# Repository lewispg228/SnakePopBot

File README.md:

OpenSnake
========================================

OpenSnake is the opensource firmware and design files that are used to produce the Electronic Snake In A Can Kit. It is a collaboration between Mario the Maker Magician and Jumping Snakes Engineering.

The classic snake-in-a-can gag meets DIY MAGIC! With this kit, you'll assemble an Electronic Snake-in-a-Can, introducing you to the world of programming, robotics, and how these tools can be used to create surprise, magic, and comedy.

* includes CONTROLLER for PLAYBACK and RECORDER of robotic magic tricks\
* RE-PROGRAMMABLE with ARDUINO
* learn about SERVOS, BUZZERS, BUTTONS, and LEDs
* pre-programmed with a magic routine written by Mario, PLUS you can make your own
* note: requires 9V battery (not included)

Buy this kit at Mario The Maker Magician's website here:

[BUY KIT HERE](https://www.mariothemagician.com/product-page/electronic-snake-in-a-can-kit)

The magic trick "skit" that is included as track one in the firmware can be watched here on Mario's Instagram post:

[INSTAGRAM VIDEO](https://www.instagram.com/tv/CCRtKZynAKZ/)

Repository Contents
-------------------

* **/Documentation** - assembly instructions, pictures, additional product information
* **/Firmware** - Arduino Code used on the snake-in-a-can controller
* **/Hardware** - Eagle design files (.brd, .sch)
* **/Hardware/Production** - Production panel files (.brd and gerbers)

License Information
-------------------

This product is _**open source**_! 

Please review the LICENSE.md file for license information. 

If you have any questions or concerns on licensing, please [file an issue on this repository](https://github.com/lewispg228/OpenSnake/issues), and we will respond asap.

Distributed as-is; no warranty is given.

- Jumping Snakes Engineering.

_<COLLABORATION CREDIT>_

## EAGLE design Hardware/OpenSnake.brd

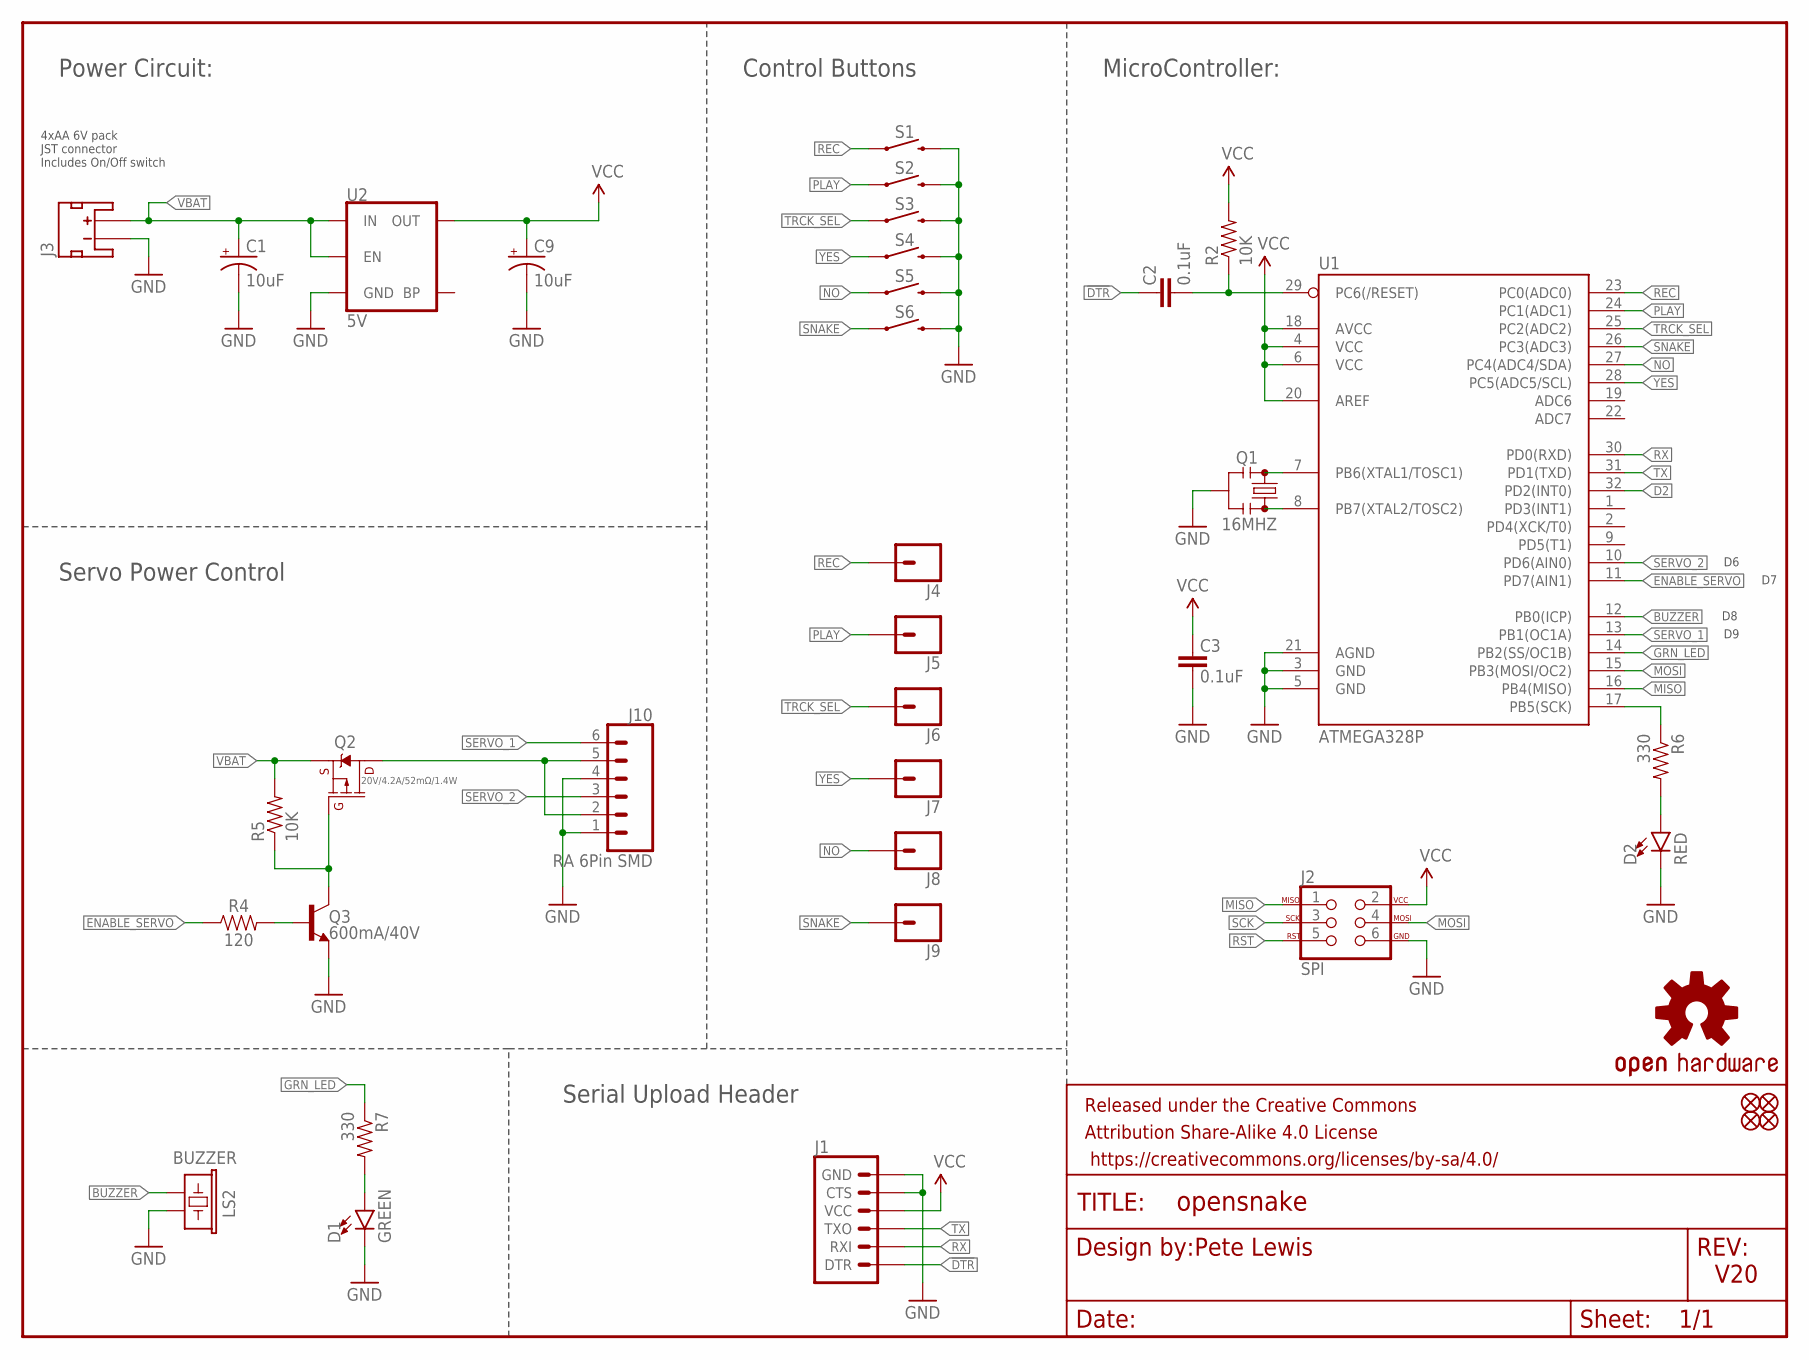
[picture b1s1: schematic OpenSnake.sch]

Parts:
C1, C9: 10uF; EIA3216
C2, C3: 0.1uF; 0603-CAP
D1: GREEN; LED-1206
D2: RED; LED-1206
FD1, FD2, FD3, FD4: FIDUCIALUFIDUCIAL; FIDUCIAL-MICRO
FRAME1: FRAME-LETTER; CREATIVE_COMMONS
J1: 6_PIN_SERIAL_TARGETSILK; 6_PIN_SERIAL_TARGET_SIDE_W_SILK
J2: SPI; 2X3_TEST_POINTS
J3: JST_2MM_MALE; JST-2-SMD
J4, J5, J6, J7, J8, J9: CONN_01PTH_NO_SILK_YES_STOP; 1X01_NO_SILK
J10: RA 6Pin SMD; 1X06-SMD_RA_MALE
LOGO1: OSHW-LOGOL; OSHW-LOGO-L
LS2: BUZZER; BUZZER-CCV
Q1: 16MHZ; RESONATOR-SMD
Q2: 20V/4.2A/52mΩ/1.4W; SOT23-3
Q3: 600mA/40V; SOT23-3
R2, R5: 10K; 0603-RES
R4: 120; 0603
R6, R7: 330; 0603-RES
S1, S2, S3, S4, S5, S6: MOMENTARY-SWITCH-SPST-SMD-5.2MM-TALL; TACTILE_SWITCH_SMD_5.2MM
U1: ATMEGA328P; TQFP32-08
U2: 5V; SOT23-5

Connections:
!DTR: C2.2, J1.P$1 (DTR)
BUZZER: LS2.- (2), U1.12 (PB0(ICP))
D2: U1.32 (PD2(INT0))
ENABLE_SERVO: R4.1, U1.11 (PD7(AIN1))
GND: C1.-, C3.1, C9.-, D1.C, D2.C, J1.P$5 (CTS), J1.P$6 (GND), J2.6, J3.1 (-), J10.1, J10.4, LS2.+ (1), Q1.2, Q3.2 (E), S1.3 (2), S2.3 (2), S3.3 (2), S4.3 (2), S5.3 (2), S6.3 (2), U1.3 (GND), U1.5 (GND), U1.21 (AGND), U2.2 (GND)
GRN_LED: R7.1, U1.14 (PB2(SS/OC1B))
MISO: J2.1, U1.16 (PB4(MISO))
MOSI: J2.4, U1.15 (PB3(MOSI/OC2))
unnamed: Q1.1, U1.8 (PB7(XTAL2/TOSC2))
unnamed: Q1.3, U1.7 (PB6(XTAL1/TOSC1))
unnamed: Q3.1 (B), R4.2
unnamed: Q2.1 (G), Q3.3 (C), R5.1
unnamed: J10.2, J10.5, Q2.3 (D)
unnamed: D2.A, R6.2
unnamed: D1.A, R7.2
NO: J8.1, S5.1, U1.27 (PC4(ADC4/SDA))
PLAY: J5.1, S2.1, U1.24 (PC1(ADC1))
REC: J4.1, S1.1, U1.23 (PC0(ADC0))
RST: C2.1, J2.5, R2.1, U1.29 (PC6(/RESET))
RX: J1.P$3 (RXI), U1.30 (PD0(RXD))
SCK: J2.3, R6.1, U1.17 (PB5(SCK))
SERVO_1: J10.6, U1.13 (PB1(OC1A))
SERVO_2: J10.3, U1.10 (PD6(AIN0))
SNAKE: J9.1, S6.1, U1.26 (PC3(ADC3))
TRCK_SEL: J6.1, S3.1, U1.25 (PC2(ADC2))
TX: J1.P$2 (TXO), U1.31 (PD1(TXD))
VBAT: C1.+, J3.2 (+), Q2.2 (S), R5.2, U2.1 (IN), U2.3 (EN)
VCC: C3.2, C9.+, J1.P$4 (VCC), J2.2, R2.2, U1.4 (VCC), U1.6 (VCC), U1.18 (AVCC), U1.20 (AREF), U2.5 (OUT)
YES: J7.1, S4.1, U1.28 (PC5(ADC5/SCL))

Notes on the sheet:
V20
Pete Lewis
Power Circuit:
4xAA 6V pack JST connector Includes On/Off switch
MicroController:
Servo Power Control
Control Buttons
Serial Upload Header

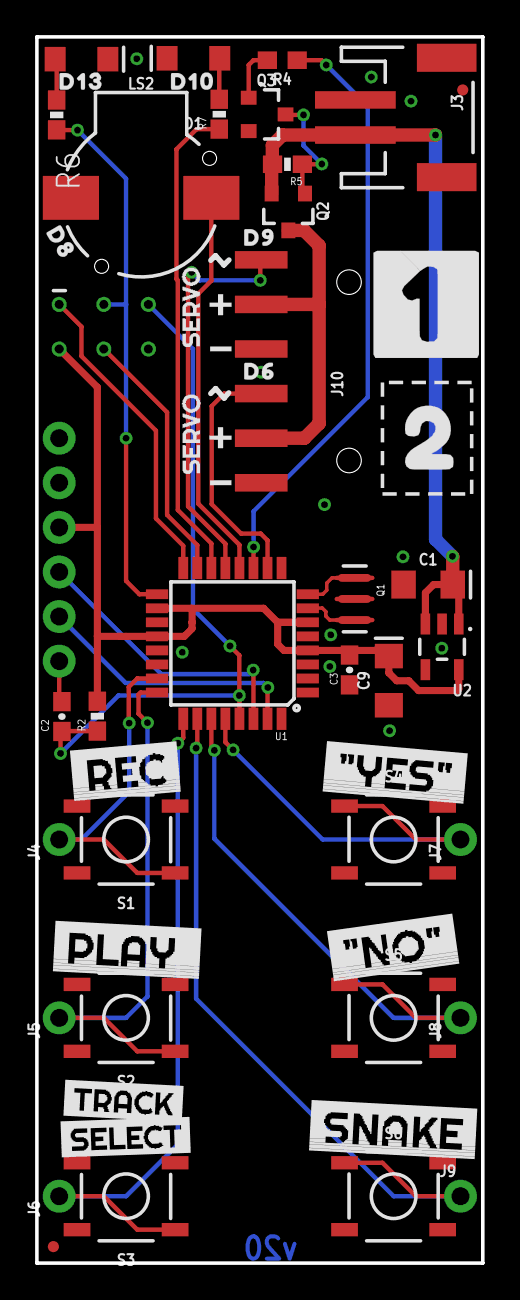
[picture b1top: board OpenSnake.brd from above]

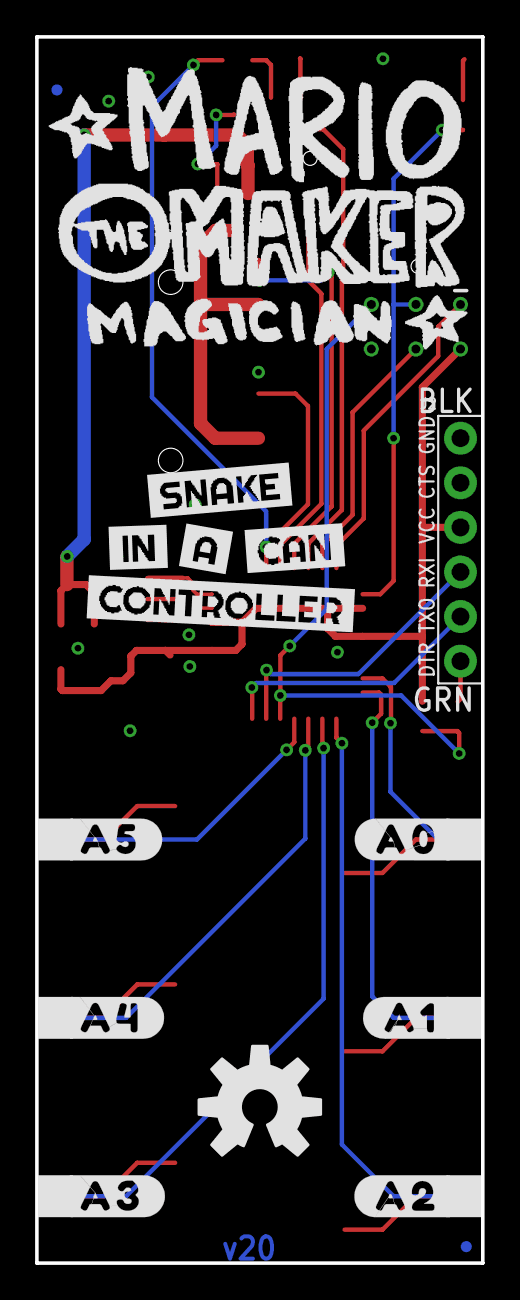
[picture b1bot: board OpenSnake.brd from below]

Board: 2 copper layers, 25.4 x 69.8 mm, 69 parts (17 on the bottom side), 28 nets.

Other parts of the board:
U$1: #A0#0
U$2: #YES#0
U$3: #NO#1
U$4: SNAKE2
U$5: MARIO_LOGO
U$6: #A1#0
U$7: #A2#0
U$8, U$13: SERVO2
U$9: #A3#0
U$10: #A4#0
U$11, U$12: #1
U$14: SNAKE0
U$15: CONTROLLER4
U$16: IN1
U$17: #A5#0
U$18: D90
U$19: REC0
U$20: PLAY_1
U$21: TRACK2
U$22: SELECT3
U$23: A2
U$24: CAN3
U$25: D60
U$26: D100
U$27: D130
U$28: D80
U$29: #1#0
U$31: 2_0

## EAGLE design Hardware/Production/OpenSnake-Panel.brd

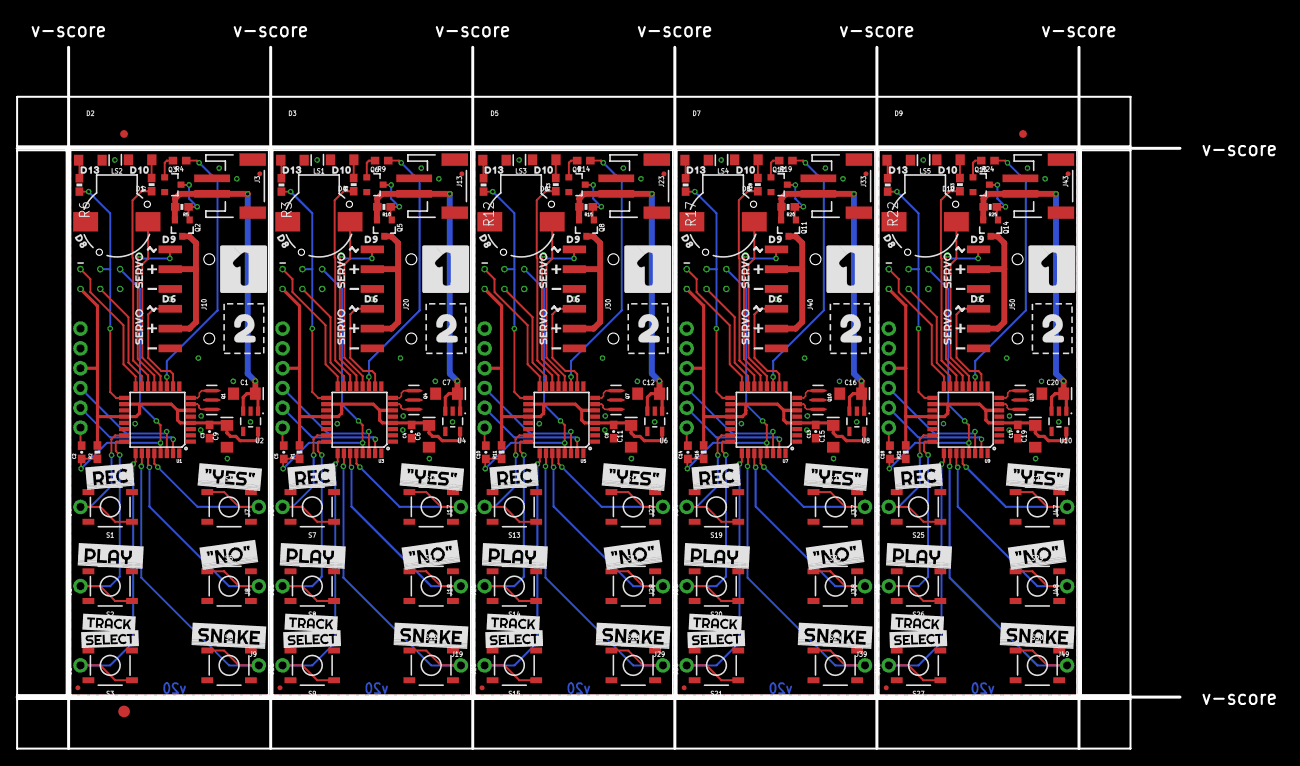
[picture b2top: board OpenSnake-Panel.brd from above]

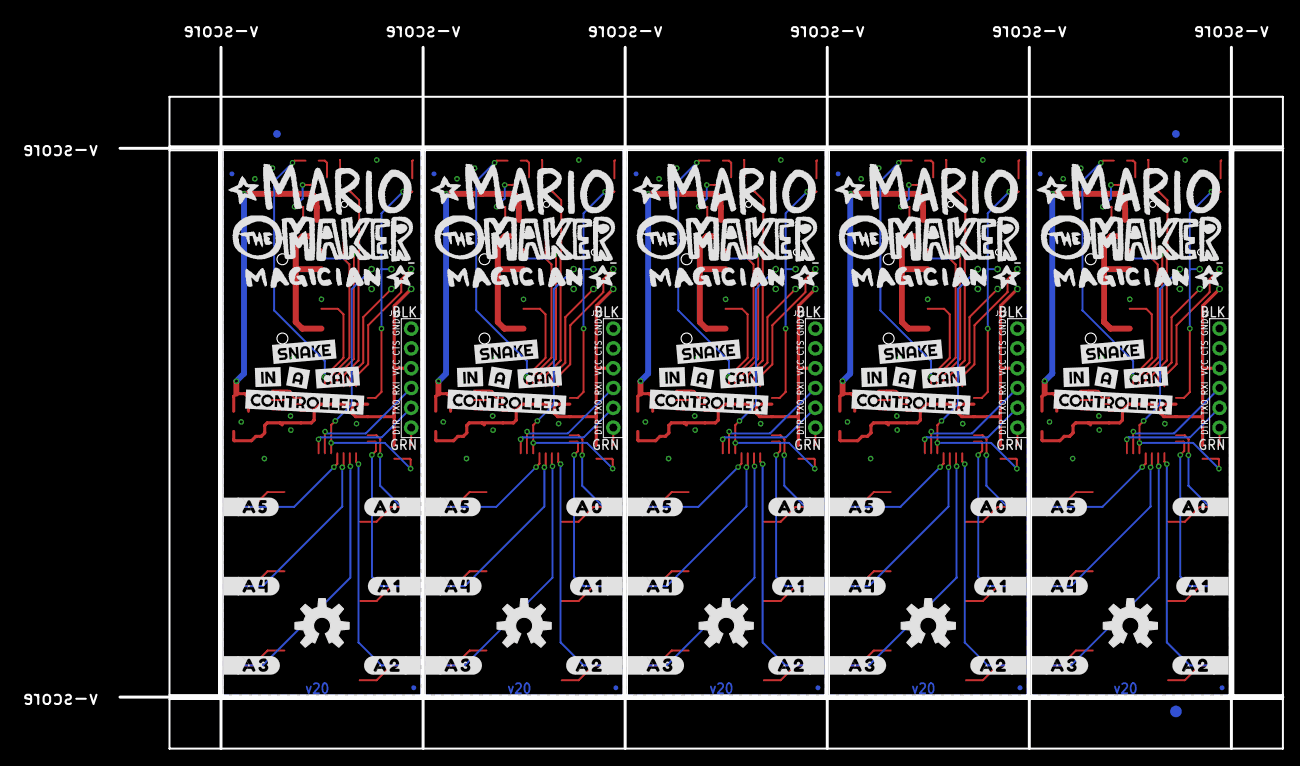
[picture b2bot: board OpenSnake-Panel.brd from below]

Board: 2 copper layers, 162.3 x 93.8 mm, 346 parts (88 on the bottom side), 140 nets.

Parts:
C1, C6, C7, C9, C11, C12, C15, C16, C19, C20: 10uF; EIA3216
C2, C3, C4, C5, C8, C10, C13, C14, C17, C18: 0.1uF; 0603-CAP
D1, D4, D6, D8, D10: GREEN; LED-1206
D2, D3, D5, D7, D9: RED; LED-1206
E$1, E$2, E$3, E$4: FIDUCIAL-1X2
E$5, E$6: FIDUCIAL-1.5X3
FD1, FD2, FD3, FD4, FD5, FD6, FD7, FD8, FD9, FD10, FD11, FD12, FD13, FD14, FD15, FD16, FD17, FD18, FD19, FD20: FIDUCIALUFIDUCIAL; FIDUCIAL-MICRO
J1, J11, J21, J31, J41: 6_PIN_SERIAL_TARGET_SIDE_W_SILK
J2, J12, J22, J32, J42: SPI; 2X3_TEST_POINTS
J3, J13, J23, J33, J43: JST-2-SMD
J4, J5, J6, J7, J8, J9, J14, J15, J16, J17, J18, J19, J24, J25, J26, J27, J28, J29, J34, J35, J36, J37, J38, J39, J44, J45, J46, J47, J48, J49: 1X01_NO_SILK
J10, J20, J30, J40, J50: RA 6Pin SMD; 1X06-SMD_RA_MALE
LOGO1, LOGO2, LOGO3, LOGO4, LOGO5: OSHW-LOGOL; OSHW-LOGO-L
LS1, LS2, LS3, LS4, LS5: BUZZER; BUZZER-CCV
Q1, Q4, Q7, Q10, Q13: 16MHZ; RESONATOR-SMD
Q2, Q5, Q8, Q11, Q14: 20V/4.2A/52mΩ/1.4W; SOT23-3
Q3, Q6, Q9, Q12, Q15: 600mA/40V; SOT23-3
R1, R2, R5, R10, R11, R15, R16, R20, R21, R25: 10K; 0603-RES
R3, R6, R7, R8, R12, R13, R17, R18, R22, R23: 330; 0603-RES
R4, R9, R14, R19, R24: 100; 0603
S1, S2, S3, S4, S5, S6, S7, S8, S9, S10, S11, S12, S13, S14, S15, S16, S17, S18, S19, S20, S21, S22, S23, S24, S25, S26, S27, S28, S29, S30: TACTILE_SWITCH_SMD_5.2MM
U1, U3, U5, U7, U9: ATMEGA328P; TQFP32-08
U2, U4, U6, U8, U10: 5V; SOT23-5
U$1, U$48, U$78, U$108, U$138: #A0#0
U$2, U$30, U$61, U$91, U$121: #YES#0
U$3, U$32, U$62, U$92, U$122: #NO#1
U$4, U$33, U$63, U$93, U$123: SNAKE2
U$5, U$38, U$68, U$98, U$128: MARIO_LOGO
U$6, U$49, U$79, U$109, U$139: #A1#0
U$7, U$50, U$80, U$110, U$140: #A2#0
U$8, U$13, U$41, U$42, U$71, U$72, U$101, U$102, U$131, U$132: SERVO2
U$9, U$51, U$81, U$111, U$141: #A3#0
U$10, U$52, U$82, U$112, U$142: #A4#0
U$11, U$12, U$39, U$40, U$69, U$70, U$99, U$100, U$129, U$130: #1
U$14, U$43, U$73, U$103, U$133: SNAKE0
U$15, U$47, U$77, U$107, U$137: CONTROLLER4
U$16, U$44, U$74, U$104, U$134: IN1
U$17, U$53, U$83, U$113, U$143: #A5#0
U$18, U$54, U$84, U$114, U$144: D90
U$19, U$34, U$64, U$94, U$124: REC0
U$20, U$35, U$65, U$95, U$125: PLAY_1
U$21, U$36, U$66, U$96, U$126: TRACK2
U$22, U$37, U$67, U$97, U$127: SELECT3
U$23, U$45, U$75, U$105, U$135: A2
U$24, U$46, U$76, U$106, U$136: CAN3
U$25, U$55, U$85, U$115, U$145: D60
U$26, U$56, U$86, U$116, U$146: D100
U$27, U$57, U$87, U$117, U$147: D130
U$28, U$58, U$88, U$118, U$148: D80
U$29, U$59, U$89, U$119, U$149: #1#0
U$31, U$60, U$90, U$120, U$150: 2_0

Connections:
!DTR: C2.2, J1.P$1
!DTR1: C5.2, J11.P$1
!DTR2: C10.2, J21.P$1
!DTR3: C14.2, J31.P$1
!DTR4: C18.2, J41.P$1
BUZZER: LS2.-, U1.12
BUZZER1: LS1.-, U3.12
BUZZER2: LS3.-, U5.12
BUZZER3: LS4.-, U7.12
BUZZER4: LS5.-, U9.12
ENABLE_SERVO: R4.1, U1.11
ENABLE_SERVO1: R9.1, U3.11
ENABLE_SERVO2: R14.1, U5.11
ENABLE_SERVO3: R19.1, U7.11
ENABLE_SERVO4: R24.1, U9.11
GND: C1.-, C3.1, C9.-, D1.C, D2.C, J1.P$5, J1.P$6, J2.6, J3.1, J10.1, J10.4, LS2.+, Q1.2, Q3.2, S1.3, S2.3, S3.3, S4.3, S5.3, S6.3, U1.3, U1.5, U1.21, U2.2
GND1: C4.1, C6.-, C7.-, D3.C, D4.C, J11.P$5, J11.P$6, J12.6, J13.1, J20.1, J20.4, LS1.+, Q4.2, Q6.2, S7.3, S8.3, S9.3, S10.3, S11.3, S12.3, U3.3, U3.5, U3.21, U4.2
GND2: C8.1, C11.-, C12.-, D5.C, D6.C, J21.P$5, J21.P$6, J22.6, J23.1, J30.1, J30.4, LS3.+, Q7.2, Q9.2, S13.3, S14.3, S15.3, S16.3, S17.3, S18.3, U5.3, U5.5, U5.21, U6.2
GND3: C13.1, C15.-, C16.-, D7.C, D8.C, J31.P$5, J31.P$6, J32.6, J33.1, J40.1, J40.4, LS4.+, Q10.2, Q12.2, S19.3, S20.3, S21.3, S22.3, S23.3, S24.3, U7.3, U7.5, U7.21, U8.2
GND4: C17.1, C19.-, C20.-, D9.C, D10.C, J41.P$5, J41.P$6, J42.6, J43.1, J50.1, J50.4, LS5.+, Q13.2, Q15.2, S25.3, S26.3, S27.3, S28.3, S29.3, S30.3, U9.3, U9.5, U9.21, U10.2
GRN_LED: R7.1, U1.14
GRN_LED1: R8.1, U3.14
GRN_LED2: R13.1, U5.14
GRN_LED3: R18.1, U7.14
GRN_LED4: R23.1, U9.14
MISO: J2.1, U1.16
MISO1: J12.1, U3.16
MISO2: J22.1, U5.16
MISO3: J32.1, U7.16
MISO4: J42.1, U9.16
MOSI: J2.4, U1.15
MOSI1: J12.4, U3.15
MOSI2: J22.4, U5.15
MOSI3: J32.4, U7.15
MOSI4: J42.4, U9.15
unnamed: Q1.1, U1.8
unnamed: Q1.3, U1.7
unnamed: D3.A, R3.2
unnamed: Q3.1, R4.2
unnamed: Q2.1, Q3.3, R5.1
unnamed: J10.2, J10.5, Q2.3
unnamed: D2.A, R6.2
unnamed: Q4.1, U3.8
unnamed: Q4.3, U3.7
unnamed: D1.A, R7.2
unnamed: J20.2, J20.5, Q5.3
unnamed: D4.A, R8.2
unnamed: Q6.1, R9.2
unnamed: Q5.1, Q6.3, R10.1
unnamed: D5.A, R12.2
unnamed: Q7.1, U5.8
unnamed: Q7.3, U5.7
unnamed: J30.2, J30.5, Q8.3
unnamed: D6.A, R13.2
unnamed: Q9.1, R14.2
unnamed: Q8.1, Q9.3, R15.1
unnamed: D7.A, R17.2
unnamed: Q10.1, U7.8
unnamed: Q10.3, U7.7
unnamed: J40.2, J40.5, Q11.3
unnamed: D8.A, R18.2
unnamed: Q12.1, R19.2
unnamed: Q11.1, Q12.3, R20.1
unnamed: D9.A, R22.2
unnamed: Q13.1, U9.8
unnamed: Q13.3, U9.7
unnamed: J50.2, J50.5, Q14.3
unnamed: D10.A, R23.2
unnamed: Q15.1, R24.2
unnamed: Q14.1, Q15.3, R25.1
NO: J8.1, S5.1, U1.27
NO1: J18.1, S11.1, U3.27
NO2: J28.1, S17.1, U5.27
NO3: J38.1, S23.1, U7.27
NO4: J48.1, S29.1, U9.27
PLAY: J5.1, S2.1, U1.24
PLAY1: J15.1, S8.1, U3.24
PLAY2: J25.1, S14.1, U5.24
PLAY3: J35.1, S20.1, U7.24
PLAY4: J45.1, S26.1, U9.24
REC: J4.1, S1.1, U1.23
REC1: J14.1, S7.1, U3.23
REC2: J24.1, S13.1, U5.23
REC3: J34.1, S19.1, U7.23
REC4: J44.1, S25.1, U9.23
RST: C2.1, J2.5, R2.1, U1.29
RST1: C5.1, J12.5, R1.1, U3.29
RST2: C10.1, J22.5, R11.1, U5.29
RST3: C14.1, J32.5, R16.1, U7.29
RST4: C18.1, J42.5, R21.1, U9.29
RX: J1.P$3, U1.30
RX1: J11.P$3, U3.30
RX2: J21.P$3, U5.30
RX3: J31.P$3, U7.30
RX4: J41.P$3, U9.30
SCK: J2.3, R6.1, U1.17
SCK1: J12.3, R3.1, U3.17
SCK2: J22.3, R12.1, U5.17
SCK3: J32.3, R17.1, U7.17
SCK4: J42.3, R22.1, U9.17
SERVO_1: J10.6, U1.13
SERVO_2: J10.3, U1.10
SERVO_3: J20.6, U3.13
SERVO_4: J20.3, U3.10
SERVO_5: J30.6, U5.13
SERVO_6: J30.3, U5.10
SERVO_7: J40.6, U7.13
SERVO_8: J40.3, U7.10
SERVO_9: J50.6, U9.13
SERVO_10: J50.3, U9.10
SNAKE: J9.1, S6.1, U1.26
SNAKE1: J19.1, S12.1, U3.26
SNAKE2: J29.1, S18.1, U5.26
SNAKE3: J39.1, S24.1, U7.26
SNAKE4: J49.1, S30.1, U9.26
TRCK_SEL: J6.1, S3.1, U1.25
TRCK_SEL1: J16.1, S9.1, U3.25
TRCK_SEL2: J26.1, S15.1, U5.25
TRCK_SEL3: J36.1, S21.1, U7.25
TRCK_SEL4: J46.1, S27.1, U9.25
TX: J1.P$2, U1.31
TX1: J11.P$2, U3.31
TX2: J21.P$2, U5.31
TX3: J31.P$2, U7.31
TX4: J41.P$2, U9.31
VBAT: C1.+, J3.2, Q2.2, R5.2, U2.1, U2.3
VBAT1: C7.+, J13.2, Q5.2, R10.2, U4.1, U4.3
VBAT2: C12.+, J23.2, Q8.2, R15.2, U6.1, U6.3
VBAT3: C16.+, J33.2, Q11.2, R20.2, U8.1, U8.3
VBAT4: C20.+, J43.2, Q14.2, R25.2, U10.1, U10.3
VCC: C3.2, C9.+, J1.P$4, J2.2, R2.2, U1.4, U1.6, U1.18, U1.20, U2.5
VCC1: C4.2, C6.+, J11.P$4, J12.2, R1.2, U3.4, U3.6, U3.18, U3.20, U4.5
VCC2: C8.2, C11.+, J21.P$4, J22.2, R11.2, U5.4, U5.6, U5.18, U5.20, U6.5
VCC3: C13.2, C15.+, J31.P$4, J32.2, R16.2, U7.4, U7.6, U7.18, U7.20, U8.5
VCC4: C17.2, C19.+, J41.P$4, J42.2, R21.2, U9.4, U9.6, U9.18, U9.20, U10.5
YES: J7.1, S4.1, U1.28
YES1: J17.1, S10.1, U3.28
YES2: J27.1, S16.1, U5.28
YES3: J37.1, S22.1, U7.28
YES4: J47.1, S28.1, U9.28

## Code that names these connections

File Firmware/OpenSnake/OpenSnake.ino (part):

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#include "pitches.h" // used for the happy birthday function

// Event types
#define YES 1
#define NO 2
#define SNAKE 3
#define LAUGH 4
#define CRY 5
#define HAPPY 6
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
#define SERVO_PWM_PIN 9
#define SERVO_PWR_CONTROL_PIN 7
#define BUZZER_PIN 8

#define RED_LED_pin 13
#define GREEN_LED_pin 10
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  Serial.begin(9600);
  Serial.println("OpenSnake Firmware Version 1.2");

  pinMode(4, OUTPUT); // buzzer low side (simon says kit)
  digitalWrite(4, LOW);   // note, other size fo buzzer is 7, and we will call that in tone, later.

  pinMode(RED_LED_pin, OUTPUT); // "NO LED"
  digitalWrite(RED_LED_pin, LOW);
  pinMode(GREEN_LED_pin, OUTPUT); // "YES LED"
  digitalWrite(GREEN_LED_pin, LOW);

  // buttons
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  Serial.println(start_mem_location);

  // Play back the track
  byte event_type = 0; // yes, no, snake, end
  int event_delay = 0; // milliseconds 0-2550

  for (int pos = start_mem_location ; pos <= (start_mem_location + 99) ; pos += 2) // because each event has a timestamp and type, we increment 2
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  digitalWrite(RED_LED_pin, LOW);
  for (int note = 150 ; note < 4000 ; note += 150)
  {
    tone(BUZZER_PIN, note, 40);
    delay(30);
  }
  noTone(BUZZER_PIN);
  digitalWrite(GREEN_LED_pin, LOW);
}

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  digitalWrite(GREEN_LED_pin, LOW);
  for (int note = 4000 ; note > 150 ; note -= 150)
  {
    tone(BUZZER_PIN, note, 30);
    delay(20);
  }
  noTone(BUZZER_PIN);
  digitalWrite(RED_LED_pin, LOW);
}

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    digitalWrite(GREEN_LED_pin, LOW);
    for (int note = 150 ; note < 4000 ; note += 150)
    {
      tone(BUZZER_PIN, note, 30);
      delay(10);
    }
    digitalWrite(RED_LED_pin, LOW);
    digitalWrite(GREEN_LED_pin, HIGH);
    for (int note = 4000 ; note > 150 ; note -= 150)
    {
      tone(BUZZER_PIN, note, 30);
      delay(10);
    }
  }

  noTone(BUZZER_PIN);

  digitalWrite(RED_LED_pin, LOW);
  digitalWrite(GREEN_LED_pin, LOW);
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  userInput = 0;
  if (digitalRead(RECORD_BUTTON) == true) recordButtonCounter = 0; // user released record button, reset counter
  if (digitalRead(TRACK_SELECT_BUTTON) == true) incrementTrackButtonCounter = 0; // user released track sel button, reset counter
  if (digitalRead(SNAKE_BUTTON) == true) snakeButtonCounter = 0; // user released snake button, reset counter

  if (digitalRead(PLAY_BUTTON) == false) userInput = PLAY_CMD;
  else if (digitalRead(RECORD_BUTTON) == false) // RECORD (note, requires long press)
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         // Refer to cry() and laugh() functions.
*/
void cry() {  // Like a dog whining
  pinMode(BUZZER_PIN, OUTPUT);
  int crydelay = 500;

  uint16_t i;
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}

void laugh() {  // Make this different than the cry - "Ha ha ha ha"
  pinMode(BUZZER_PIN, OUTPUT);
  int laughdelay = 200;
  uint16_t i;

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void playTone(uint16_t tone1, uint16_t duration) {
  if (tone1 < 50 || tone1 > 15000) return; // these do not play on a piezo
  for (long i = 0; i < duration * 1000L; i += tone1 * 2) {
    digitalWrite(BUZZER_PIN , HIGH);
    delayMicroseconds(tone1);
    digitalWrite(BUZZER_PIN , LOW);
    delayMicroseconds(tone1);
  }
}
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    }

    int noteDuration = 1130 / noteDurations[thisNote];
    tone (BUZZER_PIN, melody[thisNote], noteDuration);

    int pause = noteDuration * 1.275;
    delay (pause);

    noTone(BUZZER_PIN);
    digitalWrite(GREEN_LED_pin, LOW);
    digitalWrite(RED_LED_pin, LOW);
  }
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  myservo.write(90); // move servo
  delay(500);

  tone(BUZZER_PIN, 500, 300);
  delay(300);
  noTone(BUZZER_PIN);

  myservo.detach();  // detach() servo control pin
  digitalWrite(SERVO_PWR_CONTROL_PIN, LOW); // turn off servo power
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
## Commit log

2017-10-10 Initial layout and code
    Note, this code is for a demo that using a light sensor on pin A0, and
    so isn't *exactly* compatible with v01 of hardware. The plan for the
    default code/mode will include an RC receiver being the trigger method.
2017-10-27 Moving light sensor to look for delta
    This is now triggered by a delta (change downward) in light. So it will
    hopefully work in various light settings. The previous code had a hard
    threshold for the trigger, and so would accidentally trigger in low
    light settings.
2017-10-30 added in some debouncing on light sensor
    this seems to work better in lower light settings where the ADC may only
    return 10 or so and then only drop 5 units when you cover it up.
    The "count" variable and feature helps ensure that the noise doesn't
    cause accidental pops, and requires that the person hold their hand over
    the sensor and the reading stay "low" for at least 60 reads (with is
    roughly 120 ms - i think)
2020-01-11 Lid designs ready for cutting
2020-01-12 widened hole and moved to 1/4" for everything (except top lid)
2020-01-12 removing old dxf files
    also scooted reference line out to show middle bracer is aligned, and removed second lid dia package cause it's no longer needed.
2020-01-13 Final design on lid
    Tweaked the tightness on all the parts to fit snugly with the 1/4" acrylic (two prints at 10/100/5000). Also tweaked the drill hits to allow 4-40 to pass through easily and sevro screws to bite just 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
2020-01-14 initial idea on pcb layout
    the plan is to use some double sided tape and stick this to the side of the can. The 9V battery would also be stuck to the other side.
2020-01-21 v01 hardware ordered - Added mario logo to bottom silk - and code started
    -mario logo on bottom silk
    -v01 hardware prototypes ordered
    -Started working on the code using a simon says kit.
    -got yes, no sound functions working
    -got default tracks working and playing
    -still needs servo control implemented, but currently mapped out in snake() function
2020-02-09 Servo current spike measurements, mario graphic backup
2020-02-10 starting button control, track increment working
2020-02-16 created record_track() - not tested on hardware yet
    also created get_start_mem_location(byte track) to a function, becuase both play_track and record_track need this. Might consider moving "track" to a global variable in the future, but currently read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
    **Still need to truncate and format event_delay before sending it to record_event()
2020-02-26 Adjusted tValues for better assembly sheet, created assembly sheet PDF
2020-02-27 Corrected RX/TX to 6-pin Serial programming header
    I had these swapped on the header. Classic rookie mistake :)
    -Swapped RX/TX on the serial header
    -bumped version to v10 in sch and brd copper
2020-02-27 Optiboot hex file and added fuse settings at top of sketch
2020-02-27 Code updates for v01
    -adjusted pin definitions to work with v01 hardware. track select and play verified.
    -added in servo power control functionality, attach and detach
    -corrected comments on example 1
    -tweaked example 2 to show yes and no
    -added debug on startup to show current track, to verify that it sticks through a power cycle. It does.
    -commented out factory reset for now, during dev
2020-02-29 recording working wahoo!!
    note, I switched the buzzer pin to an unused pin during dev work. This will need to be changed back to 8 for it to work with v01 hardware.
    debounce on buttons working pretty good with initial testing. Went with a "wait for release" style. This may need to be tweaked in the future, but seems good as is for now.
2020-03-02 Factory reset caused by fresh IC or holding REC down through a pwr cycle
2020-03-11 final changes to v10
    -added green LED
    -added silk labels for servo ports
    -Panelized and cammed
2020-03-30 GREEN LED support and blink track in setup
2020-04-12 Adjusted example 1 to match video of routine 1
2020-04-21 Rec and track sel button now require long press, plus more
    -to avoid accidental presses of record or track select, they now require a "long press", so the user must hold them down for about 2 seconds to register an intended press. This is because users will 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
    -factory reset now requires user to hold down for 3 seconds.
    -snake event now includes siren sounds and green/red led blinking.
    -removed example tracks 2 and 3, to avoid confusion.
    -Cleaned up and filled in header at top of
2020-05-08 Lid and flap done. Final versions in brd and dxf files
2020-05-08 removed delay before servo detach/powerdown
    Servo moves to "open" position really quickly, so no need for this delay. When testing, I tried to move the servo during these 2 seconds, and was fighting the power/control. So I'm guessing other mig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
2020-06-05 added FW version debug and pi_grammer files
2020-06-05 corrected device type for production with atmega328 (note, no "p")
2020-07-08 lid panel files v3
2020-07-08 readme and other stuff
2020-07-08 readme graphics compression
2020-07-08 readme update
    includes new compressed graphics
2020-07-29 Lid flap and hinge wall updates
    -moved flap arm inward 0.01 inch on both sides.
    -extended flab nubbins out 0.04 inch, to make them protrude into hinge holes a bit more.
    -mitered hard corners to help avoid cracking
    -enlarged hinge nubbin hole from 0.1 inch dia to 0.12 inch dia
2020-10-22 assembly sheet optimization
    -just positioning names and values so they print nicely
2020-10-22 Lid "v4" finalized
2021-12-01 Lid and flap file cleanup
2021-12-01 v20 PCB layout - all SMD
    -Moved to high side switch with mosfet for servo power control, this will also come directly from battery (since it is now max 6V) to alleviate vreg
    -Switched to JST connector for batter input.
    -removed power switch, because the plan is to source a battery holder with switch.
    -moved to MIC5205 5V vreg, because it no longer has to power servo.
    -switched to test points for programming to make room.
    -SMD buzzer
2021-12-01 Firmware updates (v1.1)
    -Long press = snake pop (for servo horn installation)
    -If the user holds down the snake button for a "long press" (3+seconds), then the controller will move the servo to the open position. This is useful for first time setup when you need to attach the 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
    -incremented debug FW version number to v1.1
    -Use the "track select" button as a "shift" key to access laugh and cry sounds.
    -added leds to laugh and cry
    -Happy Birthday added as "track_select + snake"
2022-08-26 Auto-formatting - no functional or significant changes to code
2022-08-29 production testing added - FW v12
    -added a production testing method to more quickly test each feature of the device.

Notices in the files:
Firmware/OpenSnake/OpenSnake.ino:
License: MIT. See license file for more information but you can
parts and their libraries:
SparkFun-LED: Licensing: Creative Commons ShareAlike 4.0 International - https://creativecommons.org/licenses/by-sa/4.0
SparkFun-Aesthetics: Released under the Creative Commons Attribution Share-Alike 4.0 License
SparkFun-Aesthetics: https://creativecommons.org/licenses/by-sa/4.0
